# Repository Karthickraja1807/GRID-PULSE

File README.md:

<div align="center">

</div>

# Run and deploy your AI Studio app

This contains everything you need to run your app locally.

View your app in AI Studio: https://ai.studio/apps/764b808f-5258-4185-a244-cdf536def758

## Run Locally

**Prerequisites:**  Node.js

1. Install dependencies:
   `npm install`
2. Set the `GEMINI_API_KEY` in [.env.local](.env.local) to your Gemini API key
3. Run the app:
   `npm run dev`

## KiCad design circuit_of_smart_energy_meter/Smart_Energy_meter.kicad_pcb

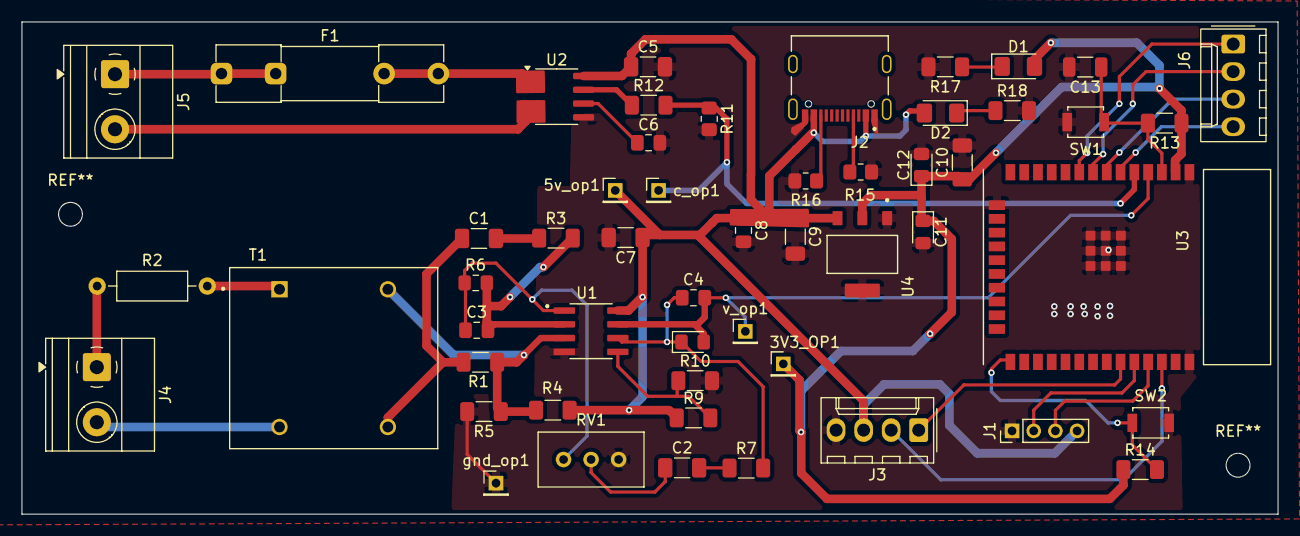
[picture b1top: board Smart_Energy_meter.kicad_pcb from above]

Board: 2 copper layers, 115.9 x 45.4 mm, 53 parts (0 on the bottom side), 36 nets.

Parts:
3V3_OP1, 5v_op1: TestPoint; PinHeader_1x01_P2.00mm_Vertical
C1, C2: 1uf; C_1206_3216Metric_Pad1.33x1.80mm_HandSolder
C3: 1nf; C_0805_2012Metric_Pad1.18x1.45mm_HandSolder
C4, C6: 1nF; C_0805_2012Metric_Pad1.18x1.45mm_HandSolder
C5: .1uF; C_1206_3216Metric_Pad1.33x1.80mm_HandSolder
C7: 100pF; C_1206_3216Metric_Pad1.33x1.80mm_HandSolder
C8: 10uF; C_0805_2012Metric_Pad1.18x1.45mm_HandSolder
C9, C10: 100nF; C_1206_3216Metric_Pad1.33x1.80mm_HandSolder
C11, C12: 10uF; D_0805_2012Metric_Pad1.15x1.40mm_HandSolder
C13: 100nf; C_1206_3216Metric
D1, D2: LED; LED_1206_3216Metric_Pad1.42x1.75mm_HandSolder
F1: Fuse; Fuseholder_Clip-5x20mm_Littelfuse_111_Inline_P20.00x5.00mm_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
J1: Conn_01x04_Pin; PinHeader_1x04_P2.00mm_Vertical
J2: TYPE-C-31-M-12; HRO_TYPE-C-31-M-12
J3, J6: Conn_01x04; Molex_KK-254_AE-6410-04A_1x04_P2.54mm_Vertical
J4: ac input; TerminalBlock_Phoenix_MKDS-1,5-2-5.08_1x02_P5.08mm_Horizont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
J5: current_i/p; TerminalBlock_Phoenix_MKDS-1,5-2-5.08_1x02_P5.08mm_Horizont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
R1: 100; R_1206_3216Metric_Pad1.30x1.75mm_HandSolder
R2: 820k; R_Axial_DIN0207_L6.3mm_D2.5mm_P10.16mm_Horizontal
R3, R4, R5, R7, R9, R10: 10k; R_1206_3216Metric_Pad1.30x1.75mm_HandSolder
R6: 100k; Fuse_0805_2012Metric_Pad1.15x1.40mm_HandSolder
R8: 100k; D_0805_2012Metric_Pad1.15x1.40mm_HandSolder
R11: 2K; R_0805_2012Metric_Pad1.20x1.40mm_HandSolder
R12: 1K; R_1206_3216Metric_Pad1.30x1.75mm_HandSolder
R13, R14: 10K; R_1206_3216Metric_Pad1.30x1.75mm_HandSolder
R15: 5.1K; R_0805_2012Metric_Pad1.20x1.40mm_HandSolder
R16: 5.1k; R_0805_2012Metric_Pad1.20x1.40mm_HandSolder
R17, R18: 100ohm; R_1206_3216Metric_Pad1.30x1.75mm_HandSolder
RV1: R_Potentiometer_Trim; Potentiometer_Bourns_3296W_Vertical
SW1, SW2: SW_Push; SW_SPST_B3U-1000P
T1: ZMPT101B; XFMR_ZMPT101B
U1: LM358; SOIC127P599X175-8N
U2: ACS712xLCTR-30A; SOIC-8_3.9x4.9mm_P1.27mm
U3: ESP32-WROOM-32E
U4: AMS1117-3.3; SOT229P700X180-4N
c_op1: TestPoint; PinHeader_1x01_P2.00mm_Vertical
gnd_op1: TestPoint; PinHeader_1x01_P2.00mm_Vertical
v_op1: TestPoint; PinHeader_1x01_P2.00mm_Vertical

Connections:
+5V: 5v_op1.1 (1_1), C5.1, C7.1, C8.1, C9.1, D2.2 (A), J1.4, J2.A4, J3.3, R4.2, R9.1, U1.8 (V+), U2.8 (VCC), U4.3 (VIN)
/3v3: 3V3_OP1.1 (1_1), C10.1, C11.1, C12.1, D1.2 (A), R13.1, R14.1, U3.2 (VDD), U4.2 (VOUT)
/IO32: J6.2, U3.8 (IO32)
/IO33: J6.1, U3.9 (IO33)
/IO34: J6.4, U3.6 (IO34)
/IO35: J6.3, U3.7 (IO35)
/Voltage_O/P: C4.2, R8.2, U1.7, U3.4 (IO36), v_op1.1 (1_1)
/bt: R14.2, SW2.1, U3.25 (IO0)
/current_o/p: R11.1, R12.2, U3.5 (IO39), c_op1.1 (1_1)
/en: C13.1, R13.2, SW1.1, U3.3 (EN)
/ol1: J3.1, U3.33 (IO21)
/ol2: J3.2, U3.36 (IO22)
/pin2: C3.2, R3.2, R6.2, U1.2 (-)
/pin3: R1.2, R4.1, R5.1, T1.4, U1.3 (+)
AC: J4.1, R2.1
GND: C5.2, C6.2, C7.2, C8.2, C9.2, C10.2, C11.2, C12.2, C13.2, J1.1, J2.A1, J3.4, R5.2, R10.2, R11.2, R15.2, R16.2, R17.2, R18.2, RV1.1, SW1.2, SW2.2, U1.4 (V-), U2.5 (GND), U3.1 (GND@1), U3.15 (GND@15), U3.38 (GND@38), U3.GND@39 (THERMAL@39), U3.GND@40 (THERMAL@39), U3.GND@41 (THERMAL@39), U3.GND@42 (THERMAL@39), U3.GND@43 (THERMAL@39), U3.GND@44 (THERMAL@39), U3.GND@45 (THERMAL@39), U3.GND@46 (THERMAL@39), U3.GND@47 (THERMAL@39), U4.1 (GND/ADJ), U4.4, gnd_op1.1 (1_1)
unnamed: C1.1, R1.1, T1.3
unnamed: C1.2, R3.1
unnamed: C2.1, RV1.2
unnamed: C2.2, R7.1
unnamed: C3.1, R6.1, RV1.3, U1.1
unnamed: D1.1 (K), R17.1
unnamed: D2.1 (K), R18.1
unnamed: F1.2, U2.1 (IP+), U2.2 (IP+)
unnamed: J1.2, U3.34 (IO3)
unnamed: J1.3, U3.35 (IO1)
unnamed: J2.A5 (CC1), R15.1
unnamed: J2.B5 (CC2), R16.1
unnamed: J4.2, T1.2
unnamed: F1.1, J5.1
unnamed: J5.2, U2.3 (IP-), U2.4 (IP-)
unnamed: R2.2, T1.1
unnamed: R9.2, R10.1, U1.5 (+)
unnamed: C4.1, R7.2, R8.1, U1.6 (-)
unnamed: C6.1, U2.6 (FILTER)
unnamed: R12.1, U2.7 (VIOUT)

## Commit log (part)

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2026-06-28 Sync latest changes from Google AI Studio
2026-06-28 Change icon for Grid Health Index
2026-06-28 Fix padding-top property in health-breakdown class
2026-06-28 Adjust padding and margin in health-breakdown class
    Fix padding and margin properties for health breakdown.
2026-06-28 Refactor health-breakdown styles
    Removed border and padding from health-breakdown class.
2026-06-29 1k to 2k
2026-06-29 1k to 5k
2026-06-29 fixed but beyond 24h
2026-06-29 fixed
